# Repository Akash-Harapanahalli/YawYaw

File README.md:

# YawYaw

### What is YawYaw?
YawYaw is a "Looky-Loo" pan and tilt camera harness designed to be mounted onto a variety of unmanned vehicles, such as UAV's, drones, and UGV's. With its built in motor array, it will provide users with a robust way to virtually interact with the surrounding environment. The easy user interface provides a hands-free solution to pan/tilt by utilizing a sensor array to track the movements of the user's head.

### How does it work?
YawYaw uses a Teensy 4.0 microprocessor to communicate with the LSM9DS1 IMU over SPI. With this data, it calculates the required power for the motors to correct their position using PID Controllers.

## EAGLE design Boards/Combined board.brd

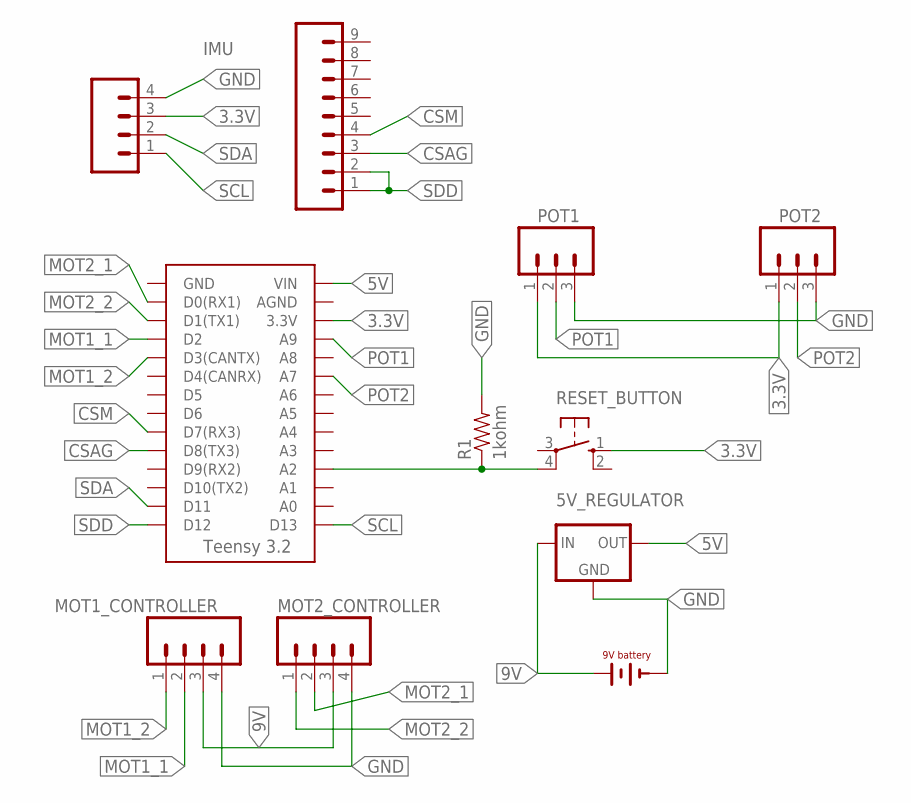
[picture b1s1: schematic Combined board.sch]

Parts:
5V_REGULATOR: OKI-78SR-5; OKI-78SR
G1: BAT9V; AB9V
IMU: M09; 1X09
JP1: M04; 1X04
MOT1_CONTROLLER, MOT2_CONTROLLER: M04; 1X04
POT1, POT2: M03; 1X03
R1: 1kohm; AXIAL-0.3
RESET_BUTTON: BTN_10-XX; B3F-10XX
U$2: TEENSY_3.2_SIMPLE

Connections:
3.3V: JP1.3, POT1.1, POT2.1, RESET_BUTTON.1 (S), U$2.3.3V
5V: 5V_REGULATOR.3 (OUT), U$2.VIN
9V: 5V_REGULATOR.1 (IN), G1.- (+), MOT1_CONTROLLER.3, MOT2_CONTROLLER.3
CSAG: IMU.3, U$2.D8(TX3)
CSM: IMU.4, U$2.D7(RX3)
GND: 5V_REGULATOR.2 (GND), G1.+ (-), JP1.4, MOT1_CONTROLLER.4, MOT2_CONTROLLER.4, POT1.3, POT2.3, R1.P$2 (2)
MOT1_1: MOT1_CONTROLLER.2, U$2.D2
MOT1_2: MOT1_CONTROLLER.1, U$2.D3(CANTX)
MOT2_1: MOT2_CONTROLLER.2, U$2.D0(RX1)
MOT2_2: MOT2_CONTROLLER.1, U$2.D1(TX1)
unnamed: R1.P$1 (1), RESET_BUTTON.4 (P1), U$2.A2
POT1: POT1.2, U$2.A9
POT2: POT2.2, U$2.A7
SCL: JP1.1, U$2.D13
SDA: JP1.2, U$2.D11
SDD: IMU.1, IMU.2, U$2.D12

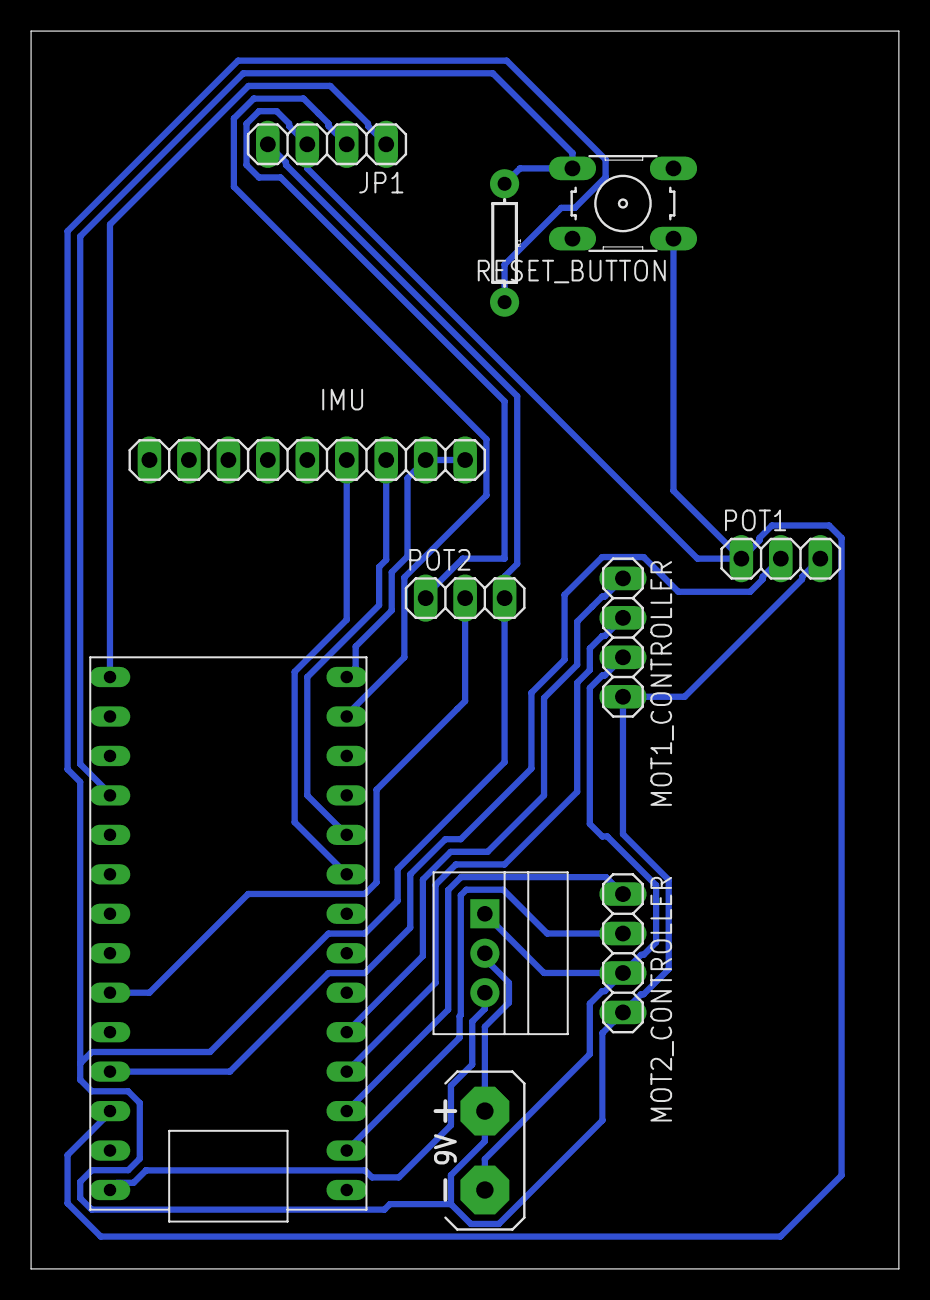
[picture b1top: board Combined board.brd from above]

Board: 2 copper layers, 55.9 x 79.7 mm, 11 parts (0 on the bottom side), 16 nets.

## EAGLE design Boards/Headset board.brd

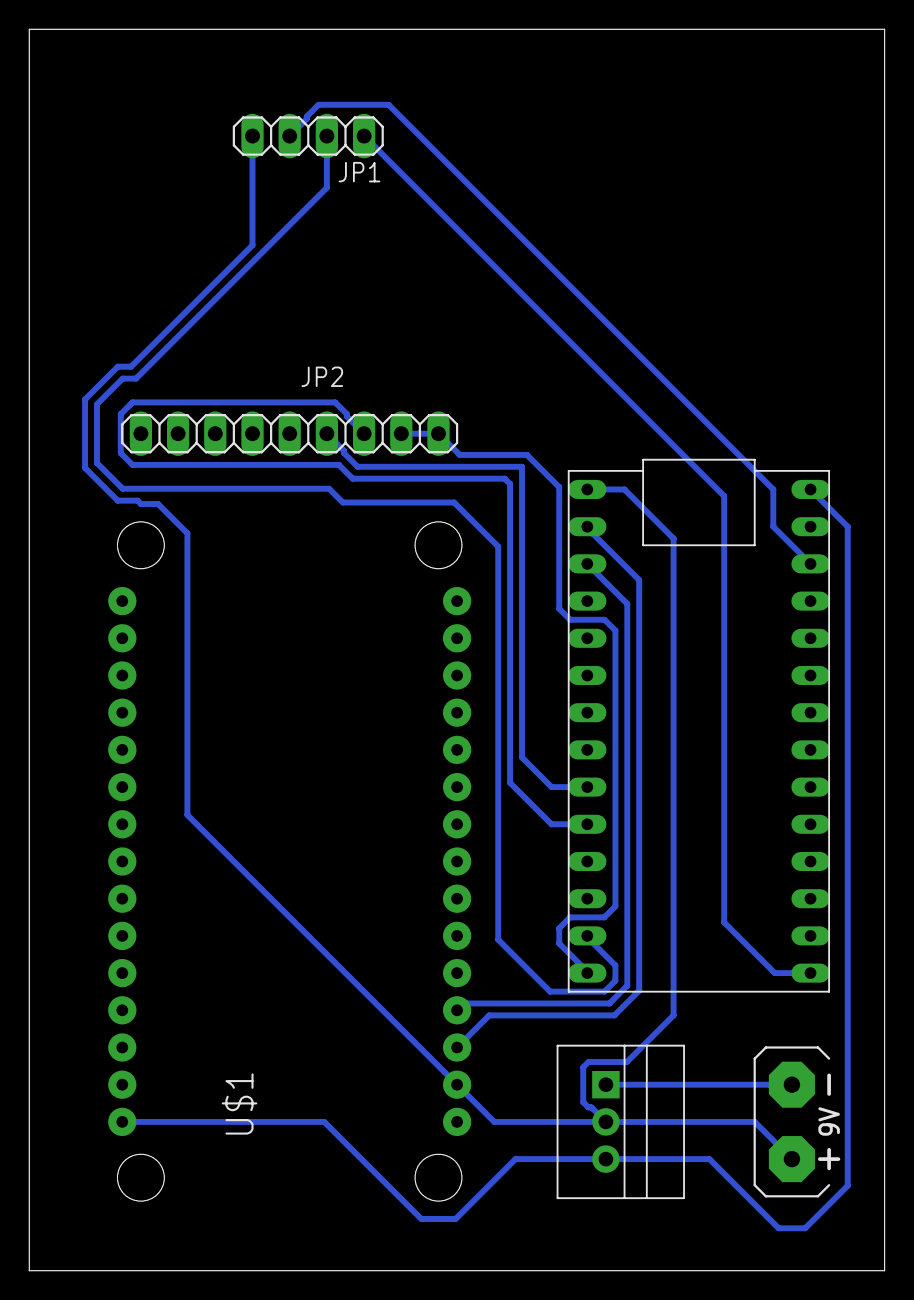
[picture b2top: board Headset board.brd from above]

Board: 2 copper layers, 58.4 x 84.8 mm, 6 parts (0 on the bottom side), 11 nets.

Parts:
G1: BAT9V; AB9V
JP1: 1X04
JP2: 1X09
U$1: ESP12E_DEVKIT
U$2: TEENSY_3.2_SIMPLE
U$3: OKI-78SR-5; OKI-78SR

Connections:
3.3V: JP1.3, U$2.3.3V
5V: U$1.VIN, U$2.VIN, U$3.3
9V: G1.-, U$3.1
CSAG: JP2.3, U$2.D8(TX3)
CSM: JP2.4, U$2.D7(RX3)
GND: G1.+, JP1.4, U$1.GND@3, U$2.GND, U$3.2
SCL: JP1.1, U$2.D13
SDA: JP1.2, U$2.D11
SDD: JP2.1, JP2.2, U$2.D12
SERIAL1: U$1.TX, U$2.D0(RX1)
SERIAL2: U$1.RX, U$2.D1(TX1)

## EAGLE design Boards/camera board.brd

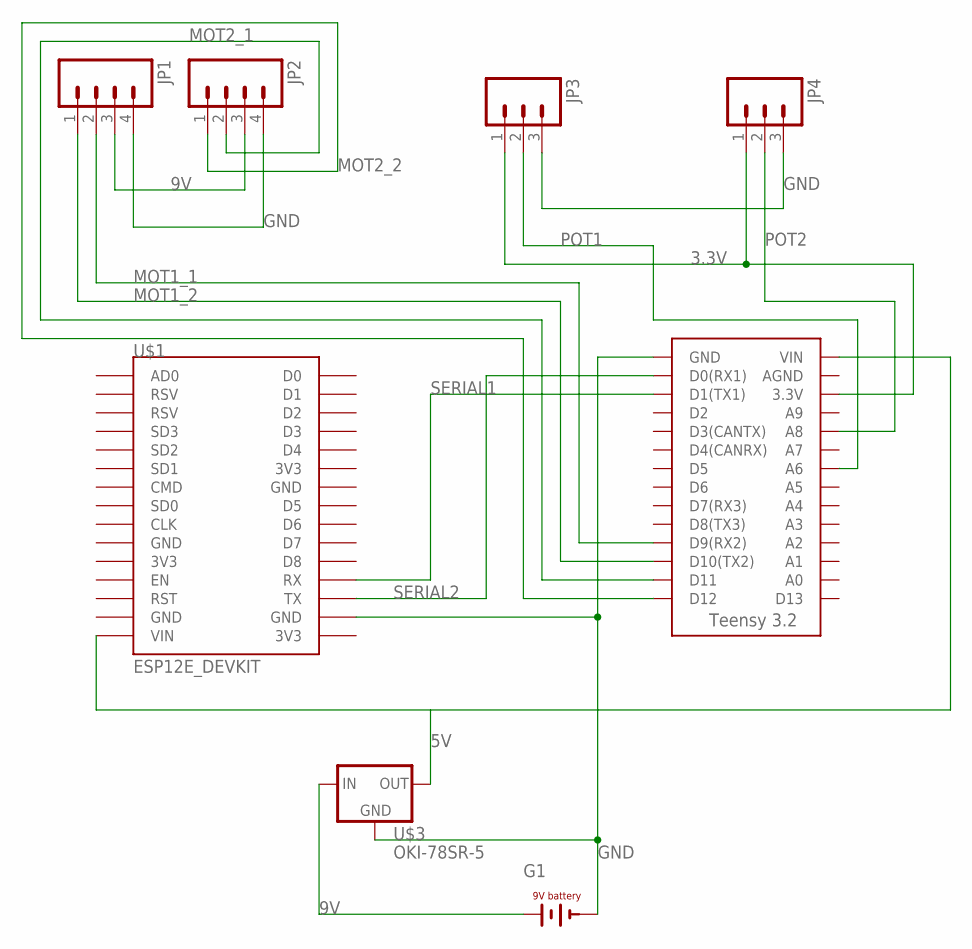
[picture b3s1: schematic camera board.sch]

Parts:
G1: BAT9V; AB9V
JP1, JP2: M04; 1X04
JP3, JP4: M03; 1X03
U$1: ESP12E_DEVKIT
U$2: TEENSY_3.2_SIMPLE
U$3: OKI-78SR-5; OKI-78SR

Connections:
3.3V: JP3.1, JP4.1, U$2.3.3V
5V: U$1.VIN, U$2.VIN, U$3.3 (OUT)
9V: G1.- (+), JP1.3, JP2.3, U$3.1 (IN)
GND: G1.+ (-), JP1.4, JP2.4, JP3.3, JP4.3, U$1.GND@3 (GND), U$2.GND, U$3.2 (GND)
MOT1_1: JP1.2, U$2.D9(RX2)
MOT1_2: JP1.1, U$2.D10(TX2)
MOT2_1: JP2.2, U$2.D11
MOT2_2: JP2.1, U$2.D12
POT1: JP3.2, U$2.A6
POT2: JP4.2, U$2.A8
SERIAL1: U$1.RX, U$2.D1(TX1)
SERIAL2: U$1.TX, U$2.D0(RX1)

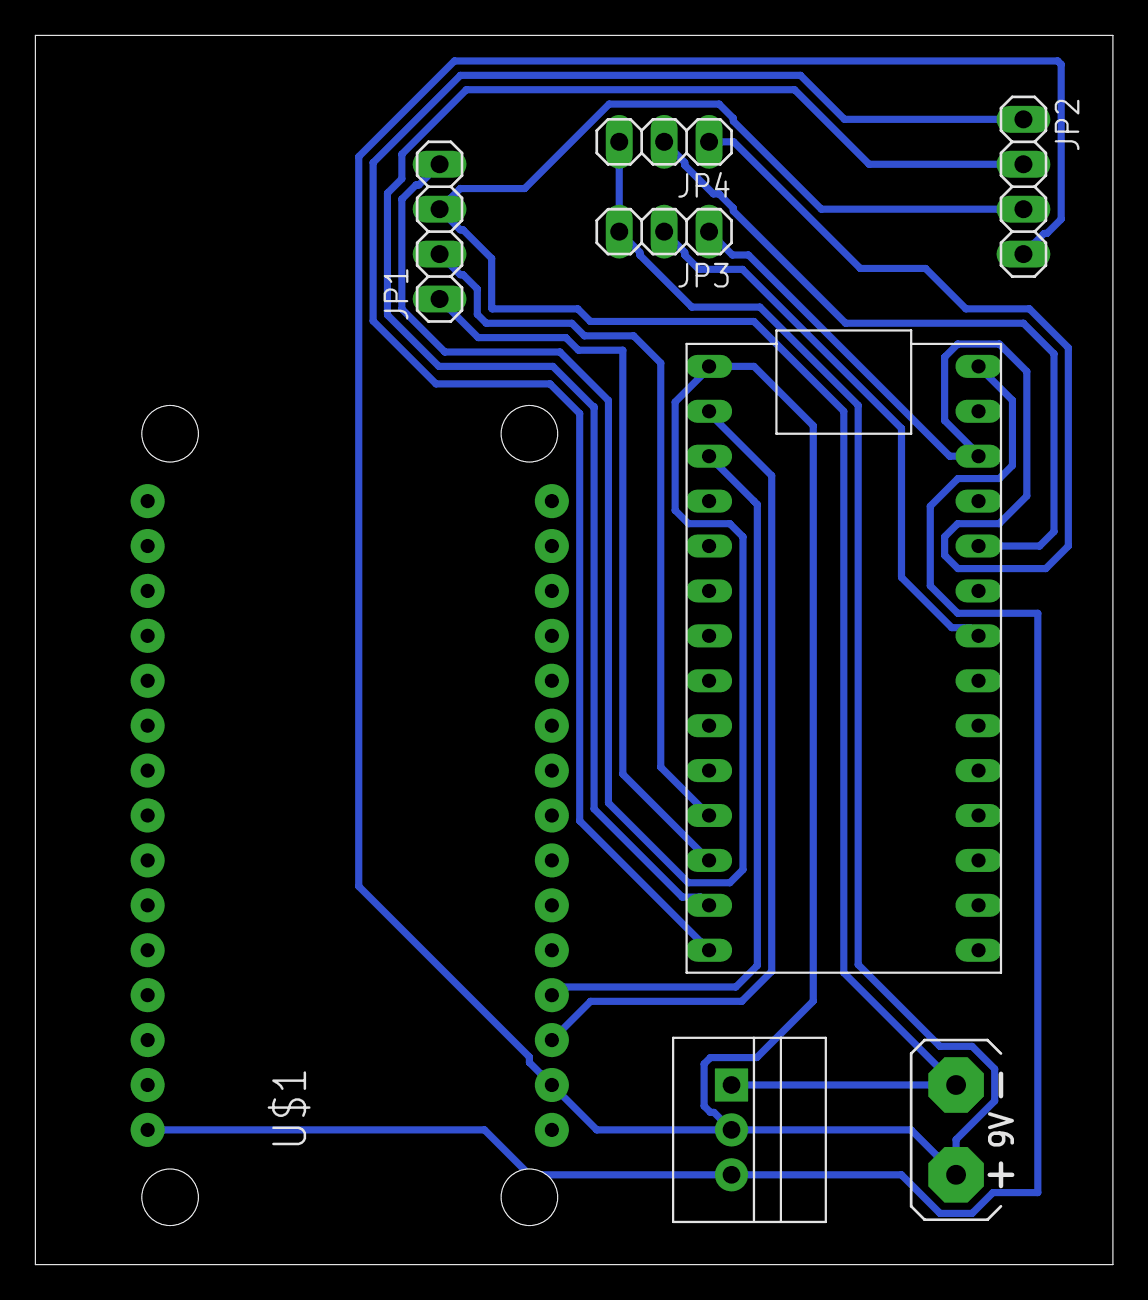
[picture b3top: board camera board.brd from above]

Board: 2 copper layers, 60.9 x 69.5 mm, 8 parts (0 on the bottom side), 12 nets.

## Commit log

2019-10-26 Wifi Comm code
    very little latency
2019-10-26 Last changes before removal of JSON
2019-10-26 Finished setting up head-controller to read sensor angles off of the imu.
2019-10-26 failed faster code
2019-10-26 Final blinky code
2019-10-26 Finished frame for camera-controller
2019-10-26 PCB Boards
    please review for my errors
2019-10-26 Minor change
2019-10-26 New Board design
2019-10-26 Board can't be printed
    :(
2019-10-27 Final commit on 2-teensy system before the merge to 1 teensy
2019-10-27 minor changes
2019-10-27 old files
2019-10-27 CNN Machine LearningCode
2019-10-27 good code
2019-10-27 Added ml
2019-10-27 stepper sadness
2019-10-27 Uncommented and finalized
2019-10-29 Final Push
